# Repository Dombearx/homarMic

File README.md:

# homarMic: pilot głosowy

Mały bezprzewodowy mikrofon „naciśnij i mów" do asystenta działającego na
komputerze w sieci domowej. Przytrzymujesz przycisk, mówisz, puszczasz.
Nagranie trafia po Wi-Fi do serwera na komputerze, a dioda potwierdza odbiór.
Między poleceniami urządzenie śpi, więc bateria starcza na tygodnie.

| | Wersja bazowa | Wersja z głośnikiem |
|---|---|---|
| Wymiary | 37 × 69 × 21 mm | 37 × 103 × 21 mm |
| Potwierdzenie | dioda RGB | dioda RGB + odpowiedź głosowa |
| Koszt części (1 szt.) | ok. 60–90 zł | ok. 75–115 zł |
| Czas pracy (30 poleceń dziennie) | ok. 2 miesiące | ok. 3–4 tygodnie |

Skąd te liczby i jak wypada własne PCB na 10 sztuk:
[docs/wybor-czesci-i-koszty.md](docs/wybor-czesci-i-koszty.md).

> **Stan projektu.** Nic z tego nie zostało jeszcze fizycznie zbudowane.
> Płytki przechodzą kontrolę DRC w KiCadzie (0 błędów elektrycznych, 0
> niepołączonych padów), modele obudowy sprawdziłem na kolizje, serwer
> przetestowałem symulowanym pilotem. Firmware'u nie udało się skompilować w
> środowisku, w którym powstał (brak dostępu do narzędzi ESP32); przeszedł tylko
> kontrolę składni. Zbuduj najpierw jedną sztukę i dopiero potem zamawiaj części
> na kolejne. Lista rzeczy do sprawdzenia jest na końcu.

## Zawartość

| Katalog | Co tam jest |
|---|---|
| `pcb/` | płytki KiCad (`voice-mic`, `voice-mic-dock`), gotowe paczki Gerber w `pcb/gerber/`, skrypt generujący |
| `case/` | model OpenSCAD i gotowe pliki STL w `case/stl/` |
| `firmware/` | program dla XIAO ESP32-S3 (PlatformIO / Arduino) |
| `server/` | serwer odbiorczy w Pythonie i symulator pilota |
| `docs/` | wybór części, kosztorysy, czas pracy |

## Jak to działa

1. Naciśnięcie przycisku budzi układ. Nagrywanie rusza po ok. 0,3 s; dioda
   zapala się na **niebiesko** dopiero wtedy, gdy mikrofon naprawdę słucha.
2. Wi-Fi łączy się w tle (ok. 1–2 s), a dźwięk w tym czasie trafia do pamięci,
   więc początek polecenia nie przepada.
3. Po puszczeniu przycisku dioda świeci na **żółto**, aż serwer odpowie.
4. **Zielony** = serwer odebrał nagranie (kod HTTP 2xx). W wersji z głośnikiem
   pilot odtwarza wtedy odpowiedź, jeśli serwer ją odesłał.
5. Układ zasypia.

| Dioda | Znaczenie |
|---|---|
| niebieska | nagrywam, mów |
| żółta | wysyłam / czekam na odpowiedź |
| zielona | polecenie odebrane |
| 3 × czerwona | błąd: brak Wi-Fi, serwer nie odpowiada albo zwrócił błąd |
| 2 × długa czerwona po poleceniu | słaba bateria, odłóż do stacji |
| 2 × biała | po włączeniu zasilania: układ działa (czerwona = słaba bateria) |

Naciśnięcie krótsze niż 0,25 s jest ignorowane. Jedno polecenie może trwać do
30 s.

## Lista części

Ceny orientacyjne z listopada 2026. Niższa wartość to AliExpress, wyższa to
polskie sklepy.

### Pilot, wersja bazowa

| Oznaczenie | Część | Szt. | Cena |
|---|---|---|---|
| U1 | Seeed Studio XIAO ESP32-S3 (zwykły, nie Sense, nie Plus), z antenką | 1 | 30–45 zł |
| — | moduł mikrofonu I2S INMP441 (okrągły, 14 mm) | 1 | 7–15 zł |
| — | akumulator LiPo 3,7 V 500 mAh typu 502535 **z zabezpieczeniem** (PCM) | 1 | 12–20 zł |
| — | płytka `voice-mic` | 1 | 5–8 zł |
| SW1 | mikroprzycisk 6 × 6 mm, THT, wysokość 5 mm | 1 | 0,30 zł |
| D1 | dioda RGB 5 mm, wspólna katoda, matowa | 1 | 0,50 zł |
| D2 | dioda Schottky'ego SS14 (SMA) | 1 | 0,30 zł |
| R1 | 470 Ω, 1206 | 1 | grosze |
| R2, R3 | 220 Ω, 1206 | 2 | |
| R4 | 100 kΩ, 1206 | 1 | |
| R5, R6 | 470 kΩ, 1206 | 2 | |
| C1 | 100 nF, 1206 | 1 | |
| — | wkręty M2 × 12 (do plastiku lub zwykłe) | 4 | 1 zł |
| — | śruby M3 × 8 z łbem kulistym na imbus (ISO 7380) + nakrętki M3 | 2 + 2 | 1 zł |
| — | magnes neodymowy 8 × 3 mm | 1 | 1 zł |
| — | przewód cienki (np. kynar/silikon 28–30 AWG), ok. 40 cm | | |
| — | filament PETG lub PLA, ok. 25 g | | 2 zł |

### Dodatkowo w wersji z głośnikiem

| Oznaczenie | Część | Szt. | Cena |
|---|---|---|---|
| — | moduł wzmacniacza I2S MAX98357A (układ pinów jak Adafruit: LRC, BCLK, DIN, GAIN, SD, GND, VIN) | 1 | 8–15 zł |
| — | głośnik 28 mm, 8 Ω, 1–2 W | 1 | 5–8 zł |
| R7 | 10 kΩ, 1206 | 1 | grosze |
| C2 | 10 µF, 1206 | 1 | grosze |
| — | wkręty M2 × 12 | 2 | |

### Stacja dokująca

| Część | Szt. | Cena |
|---|---|---|
| płytka `voice-mic-dock` | 1 | 3 zł |
| pin sprężynowy (pogo) do lutowania THT, średnica korpusu 2 mm, wysokość ok. 7 mm, trzpień do 1,2 mm | 2 | 2–4 zł |
| magnes neodymowy 8 × 3 mm | 1 | 1 zł |
| przewód USB (stary kabel z wtykiem USB-A lub gniazdo USB-C „breakout" z rezystorami 5,1 kΩ) | 1 | 0–4 zł |
| wkręty M2 × 5 | 2 | |
| filament, ok. 35 g | | 3 zł |

Jedna stacja może obsługiwać kilka pilotów po kolei. Ładowanie do pełna trwa
ok. 10–11 h (XIAO ładuje prądem 50 mA), więc najwygodniej, żeby pilot po
prostu stał w stacji, gdy go nie używasz.

## Krok 1. Zamów płytki

Paczki `pcb/gerber/voice-mic-gerber.zip` i `pcb/gerber/voice-mic-dock-gerber.zip`
wgraj jako dwa osobne zamówienia (JLCPCB, PCBWay, Aisler). Parametry:
2 warstwy, FR-4, **1,6 mm**, miedź 1 oz, dowolny kolor, wykończenie HASL.
Minimalna ilość to zwykle 5 sztuk, czyli od razu masz płytki na 5 pilotów.

## Krok 2. Wydrukuj obudowę

Pliki z `case/stl/`. PETG lub PLA, warstwa 0,2 mm, 3 obrysy, wypełnienie 20%,
**bez podpór**. Części są już ułożone do druku.

| Plik | Ułożenie |
|---|---|
| `tub.stl` / `tub-speaker.stl` | przednią ścianką do stołu |
| `lid.stl` / `lid-speaker.stl` | zewnętrzną stroną do stołu |
| `button.stl` | klawiszem do stołu |
| `dock.stl` | tak jak stoi |

Wymiary zmienisz w `case/voice_mic.scad` (wszystko jest w parametrach na
górze pliku), a potem:

```bash
openscad -D 'part="tub"' -D speaker=false -o tub.stl voice_mic.scad
```

Najczęściej trzeba będzie dopasować `mic_shape` / `mic_d` (moduły INMP441
bywają okrągłe albo kwadratowe 14 × 14 mm) oraz `pogo_body` i `pogo_hole` do
kupionych pinów pogo.

## Krok 3. Zlutuj płytkę pilota

Wszystko da się zlutować zwykłą lutownicą z cienkim grotem. Kolejność ma
znaczenie.

1. **Elementy SMD** (przód płytki): R1–R6, C1, D2. Pasek na D2 (katoda) jest
   po stronie dolnej krawędzi płytki, czyli od strony USB. W wersji z
   głośnikiem także R7 i C2.
2. **Moduł XIAO.** Połóż go płasko na przedzie płytki, gniazdem USB w stronę
   dolnej krawędzi (gniazdo wystaje ok. 1,5 mm poza płytkę). Wyrównaj pady
   krawędziowe, przylutuj dwa po przekątnej, sprawdź ułożenie, potem pozostałe
   12.
3. **Pady baterii XIAO.** Odwróć płytkę. Pod modułem są dwa owalne otwory
   opisane na tylnej stronie. Przyłóż grot do otworu, podaj cynę i trzymaj
   2–3 s, aż wypełni otwór i złapie pad na spodzie modułu. Zrób to dla obu.
   Bez tego pilot działa tylko z USB.
4. **Przycisk SW1.**
5. **Mikrofon.** Przylutuj 6 przewodów długości ok. 25 mm do pól `MIC`
   (VDD, GND, SD, SCK, WS, L/R) i do tak samo opisanych pól modułu INMP441.
   Kolejność pól na module bywa różna, kieruj się opisami, nie położeniem.
6. **Dioda D1.** Włóż ją w płytkę, ale jeszcze nie lutuj. Najdłuższa nóżka
   (wspólna katoda) idzie do drugiego otworu od lewej. Włóż płytkę do
   wydrukowanej wanny, dosuń diodę tak, żeby czubek był równo z powierzchnią
   obudowy, i dopiero wtedy przylutuj nóżki od tyłu.
7. **Antena.** Wepnij dołączoną antenkę w złącze na module XIAO.
8. **Wersja z głośnikiem:** moduł MAX98357A lutujesz od **tylnej** strony
   płytki do pól `AMP`, elementami do tyłu, tak żeby wystawał ponad górną
   krawędź płytki. Opisy pól na płytce (VIN, GND, SD, GAIN, DIN, BCLK, LRC)
   muszą się pokryć z opisami na module. Głośnik przylutuj dwoma przewodami do
   wyjścia modułu.

Baterii jeszcze nie podłączaj.

## Krok 4. Wgraj program i przetestuj na kablu

```bash
cd firmware
cp include/config.example.h include/config.h
```

W `include/config.h` wpisz nazwę i hasło Wi-Fi, adres komputera z asystentem
i ewentualnie `HAS_SPEAKER 1`. Potem podłącz pilota kablem USB-C:

```bash
pio run -t upload
```

```bash
pio device monitor
```

Jeśli komputer nie widzi portu, przytrzymaj malutki przycisk `B` (BOOT) na
module XIAO i dopiero wtedy wepnij kabel. To samo zrób przy każdym kolejnym
wgrywaniu, bo śpiący układ odłącza się od USB.

W Arduino IDE: płytka „XIAO_ESP32S3", **PSRAM: OPI PSRAM**, USB CDC On Boot:
Enabled; pliki `src/main.cpp` i `include/config.h` wrzuć do jednego szkicu.

Uruchom serwer (krok 6), przytrzymaj przycisk, powiedz coś, puść. Powinieneś
zobaczyć niebieski, żółty i zielony, a w katalogu `server/recordings/` plik
WAV. Odsłuchaj go. Jeśli jest za cicho lub przesterowane, zmień
`MIC_GAIN_SHIFT` w `config.h`. Jeśli kolory diody są zamienione (diody RGB
mają różne układy nóżek), zamień numery `PIN_LED_R/G/B` w `main.cpp`.

## Krok 5. Bateria, styki i składanie

1. **Bateria.** Sprawdź miernikiem biegunowość przewodów. Czerwony do `BAT+`,
   czarny do `BAT-`. Lutuj po jednym przewodzie i nie zwieraj ich ze sobą.
   Po podłączeniu dioda mignie dwa razy na biało.
2. **Styki ładowania.** W dolną ściankę wanny wkręć od zewnątrz dwie śruby
   M3 × 8. Od środka załóż na każdą oczko z odizolowanego przewodu i dokręć
   nakrętką. Patrząc od przodu (przycisk do ciebie, USB na dole): lewa śruba
   to `DOCK+`, prawa `DOCK-`. Przylutuj przewody do tak opisanych pól płytki.
   Na stykach nie ma napięcia, gdy pilot nie stoi w stacji.
3. **Magnes.** Wklej magnes w okrągłe gniazdo w dolnej ściance (od środka,
   między śrubami). Zrób to przed włożeniem płytki.
4. Włóż klawisz w otwór wanny (kołnierzem do środka).
5. Wsuń moduł mikrofonu w okrągłe gniazdo na przedniej ściance, **stroną z
   otworkiem do ścianki**, puszką mikrofonu do środka. Przyklej kroplą kleju
   przy krawędzi, nie zalewając otworka.
6. Wersja z głośnikiem: wklej głośnik membraną do kratki.
7. Połóż płytkę na słupkach, gniazdem USB w otwór dolnej ścianki.
8. Baterię przyklej taśmą piankową do tyłu płytki, między tulejami pokrywy.
   Antenę przyklej do bocznej ścianki, z dala od baterii.
9. Załóż pokrywę i skręć czterema wkrętami M2 × 12 (sześcioma w wersji z
   głośnikiem). Wkręty przechodzą przez płytkę i trzymają wszystko razem.

## Krok 6. Stacja dokująca

1. Wklej magnes w gniazdo od spodu podłogi stacji. **Sprawdź biegun:** musi
   przyciągać magnes w pilocie, nie odpychać.
2. Przylutuj dwa piny pogo do płytki stacji, a do pól `+` i `-` przewód 5 V
   z kabla USB (czerwony = +5 V, czarny = masa).
3. Wsuń płytkę pinami do góry w komorę od spodu i przykręć dwoma wkrętami
   M2 × 5. Piny powinny wystawać ok. 1,3 mm ponad podłogę. Pin `+5V` musi
   wypaść pod lewą śrubą pilota (patrząc od strony wycięcia w stacji).
4. Przewód wyprowadź kanałem do tyłu i unieruchom kroplą kleju.
5. Zmierz miernikiem: między pinami ma być 5 V, plus po właściwej stronie.

Pilot wstawiasz przyciskiem w stronę wycięcia. Włożony odwrotnie po prostu
się nie ładuje (dioda D2 chroni przed odwrotną biegunowością). Ładowanie
sygnalizuje czerwona dioda na module XIAO, widoczna przez szczelinę przy
gnieździe USB.

## Krok 7. Serwer na komputerze

Serwer wzorcowy nie ma żadnych zależności poza Pythonem 3.8+:

```bash
python3 server/voice_server.py --port 8765
```

Zapisuje każde polecenie jako WAV (16 kHz, 16 bit, mono) w `recordings/`.
Żeby od razu przekazywać nagrania do agenta:

```bash
python3 server/voice_server.py --exec "python3 moj_agent.py"
```

Po każdym nagraniu uruchomi się `moj_agent.py <ścieżka.wav>`. Jeśli program
wypisze na standardowe wyjście ścieżkę do pliku `.wav`, a pilot ma głośnik,
ten plik wróci do pilota jako odpowiedź głosowa (WAV, PCM 16 bit, mono,
najlepiej 16–24 kHz).

Możesz też wbudować odbiór we własnego agenta:

```python
from voice_server import serve

def handle(wav_path, meta):   # meta: device, battery_mv, speaker, seconds
    tekst = transkrybuj(wav_path)      # np. faster-whisper
    odpowiedz = agent(tekst, zrodlo=meta["device"])
    return None                        # albo ścieżka / bajty WAV z odpowiedzią

serve(handle, port=8765)
```

Zielona dioda zapala się dopiero, gdy `handle` się zakończy, więc jeśli agent
myśli długo, uruchom go w tle i wróć od razu. Wyjątek w `handle` daje kod 500
i czerwoną diodę.

Bez pilota przetestujesz serwer tak:

```bash
python3 server/fake_mic.py --host 127.0.0.1
```

Zapora systemowa musi przepuszczać port 8765 z sieci lokalnej. Komputerowi
warto nadać stały adres IP w routerze.

### Protokół (gdybyś pisał własny odbiornik)

```
POST /api/voice HTTP/1.1
Transfer-Encoding: chunked
Content-Type: application/octet-stream
X-Audio-Format: pcm_s16le
X-Sample-Rate: 16000
X-Channels: 1
X-Device-Id: mic-a1b2c3        nazwa pilota (z config.h albo z adresu MAC)
X-Battery-Mv: 3912
X-Speaker: 0                   1 = pilot potrafi odtworzyć odpowiedź
X-Auth-Token: ...              tylko gdy ustawiony w config.h

<surowe próbki PCM, little-endian>
```

Odpowiedź: dowolny kod 2xx oznacza „odebrane". Jeśli `Content-Type` to
`audio/wav` i podany jest `Content-Length`, wersja z głośnikiem odtworzy
treść. Odpowiedź musi mieć `Content-Length` (bez `chunked`). Na odpowiedź
pilot czeka do 30 s.

## Wiele pilotów

Każdy pilot ma ten sam program. Rozróżnia je nagłówek `X-Device-Id`; domyślnie
to `mic-` plus końcówka adresu MAC, a w `config.h` możesz wpisać własną nazwę
(np. `kuchnia`) przed wgraniem. Serwer obsługuje wiele pilotów jednocześnie.

## Problemy

| Objaw | Co sprawdzić |
|---|---|
| Działa na USB, nie działa na baterii | otwory `BAT+`/`BAT-` pod XIAO nie złapały padów modułu; dolutuj od tyłu |
| 3 × czerwona zaraz po puszczeniu | serwer nie działa, zły adres w `config.h` albo zapora |
| 3 × czerwona po ok. 10 s | brak połączenia z Wi-Fi (hasło, zasięg, sieć tylko 5 GHz; ESP32 potrzebuje 2,4 GHz) |
| Nagranie to cisza | zamienione przewody SD/SCK/WS albo `L/R` nie jest na masie |
| Ucięty początek polecenia | zacznij mówić, gdy zapali się niebieska dioda |
| Klawisz nie klika albo jest stale wciśnięty | inna wysokość mikroprzycisku; zmień `sw_h` w pliku SCAD |
| Nie ładuje w stacji | odwrócona biegunowość pinów, za krótkie piny, magnes odpycha |
| Bateria pada po kilku dniach | zmierz prąd uśpienia (powinno być ok. 20 µA); patrz niżej |

## Do sprawdzenia przy pierwszej sztuce

- Kompilacja firmware'u prawdziwym narzędziem (PlatformIO). Program używa
  starszego sterownika I2S (`driver/i2s.h`), który działa z rdzeniem Arduino
  ESP32 2.x i 3.x.
- Prąd uśpienia. Seeed podaje 14 µA dla XIAO ESP32-S3, dzielnik baterii
  dokłada ok. 4,5 µA. Niektóre niezależne pomiary pokazują wyraźnie więcej,
  więc zmierz to miernikiem włączonym szeregowo z baterią.
- Dopasowanie modułu INMP441 do gniazda i pinów pogo do stacji (części z
  AliExpress różnią się wymiarami między sprzedawcami).
- Siła magnesu względem nacisku pinów pogo: pilot ma sam dosiadać w stacji.
  Jeśli „pływa" na pinach, weź piny o mniejszym nacisku albo mocniejszy
  magnes (parametry `magnet_d`, `magnet_h`).
- Luz klawisza i głębokość gniazda USB-C z twoim kablem.

## Zmiany w płytce

Płytki powstają ze skryptu `pcb/gen_pcb.py` (wymaga KiCada 7 lub nowszego z
modułem `pcbnew`); rozmieszczenie, sieci i opisy są w nim zapisane wprost,
a ścieżki prowadzi `pcb/router.py`. Pliki `.kicad_pcb` można też po prostu
otworzyć i poprawić ręcznie w KiCadzie. Schemat połączeń jest w
[docs/wybor-czesci-i-koszty.md](docs/wybor-czesci-i-koszty.md#schemat-połączeń).
Wymiary padów modułu XIAO pochodzą z biblioteki Seeed Studio OPL (CC BY-SA 4.0).

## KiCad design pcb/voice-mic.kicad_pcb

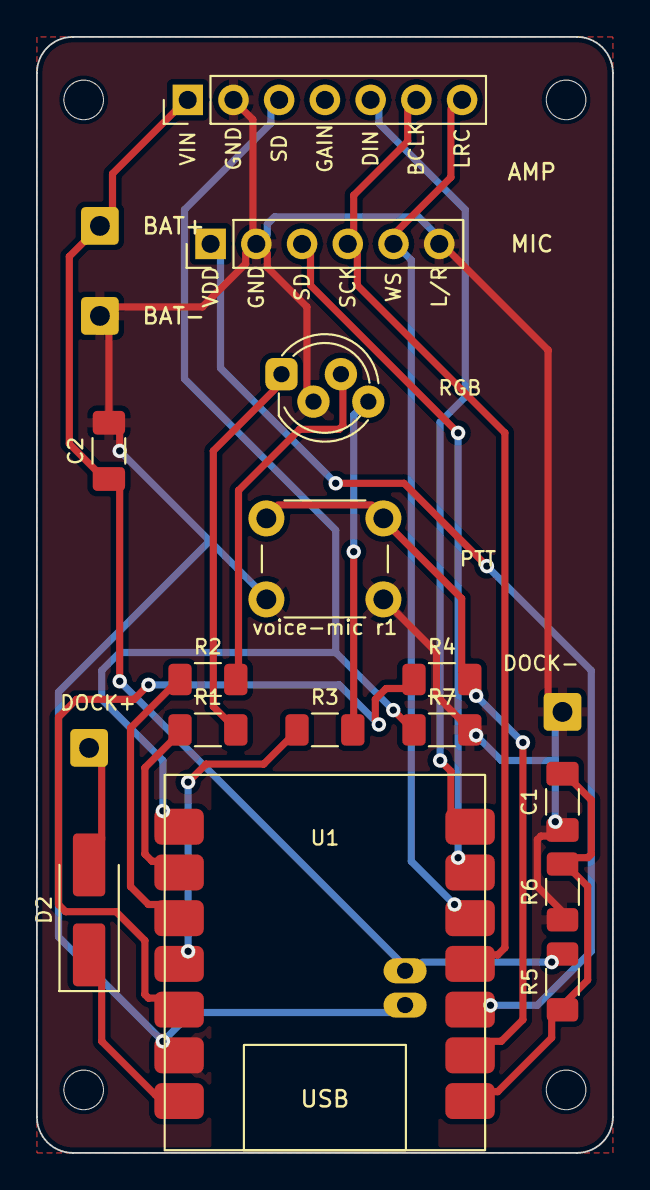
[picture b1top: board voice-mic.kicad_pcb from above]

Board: 2 copper layers, 32.0 x 62.0 mm, 23 parts (0 on the bottom side), 19 nets.

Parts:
C1: 100n; C_1206_3216Metric_Pad1.33x1.80mm_HandSolder
C2: 10u; C_1206_3216Metric_Pad1.33x1.80mm_HandSolder
D1: RGB 5mm wsp. katoda; LED_D5.0mm-4_RGB_Staggered_Pins
D2: SS14; D_SMA_Handsoldering
H1, H2, H3, H4: M2; MountingHole_2.2mm_M2
J1: INMP441; PinHeader_1x06_P2.54mm_Vertical
J2: MAX98357A; PinHeader_1x07_P2.54mm_Vertical
J3: BAT+; SolderWire-0.5sqmm_1x01_D0.9mm_OD2.1mm
J4: DOCK+; SolderWire-0.5sqmm_1x01_D0.9mm_OD2.1mm
J5: DOCK-; SolderWire-0.5sqmm_1x01_D0.9mm_OD2.1mm
J6: BAT-; SolderWire-0.5sqmm_1x01_D0.9mm_OD2.1mm
R1: 470R; R_1206_3216Metric_Pad1.30x1.75mm_HandSolder
R2, R3: 220R; R_1206_3216Metric_Pad1.30x1.75mm_HandSolder
R4: 100k; R_1206_3216Metric_Pad1.30x1.75mm_HandSolder
R5, R6: 470k; R_1206_3216Metric_Pad1.30x1.75mm_HandSolder
R7: 10k; R_1206_3216Metric_Pad1.30x1.75mm_HandSolder
SW1: 6x6x5; SW_PUSH_6mm_H5mm
U1: XIAO ESP32-S3

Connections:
+3V3: R4.1, U1.12
AMP_DIN: J2.5, U1.7
AMP_SD: J2.3, R7.1, U1.8
BAT_SENSE: C1.2, R5.1, R6.2, U1.1
BTN: R4.2, SW1.1, U1.2
DOCK_P: D2.2, J4.1
GND: C1.1, C2.2, D1.2, J1.2, J1.6, J2.2, J5.1, J6.1, R6.1, R7.2, SW1.2, U1.13, U1.24
I2S_BCLK: J1.4, J2.6, U1.4
I2S_WS: J1.5, J2.7, U1.5
LED_B: R3.1, U1.11
LED_BA: D1.4, R3.2
LED_G: R2.1, U1.10
LED_GA: D1.3, R2.2
LED_R: R1.1, U1.9
LED_RA: D1.1, R1.2
MIC_PWR: J1.1, U1.3
MIC_SD: J1.3, U1.6
VBAT: C2.1, J2.1, J3.1, R5.2, U1.23
VBUS: D2.1, U1.14

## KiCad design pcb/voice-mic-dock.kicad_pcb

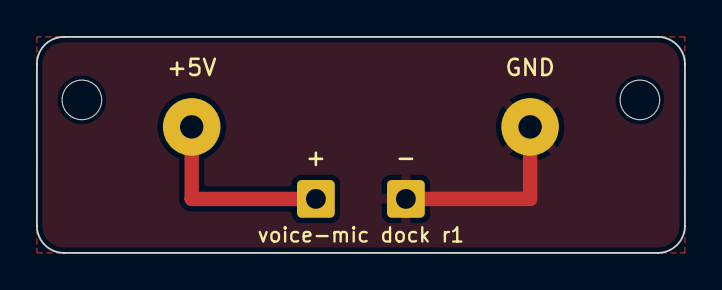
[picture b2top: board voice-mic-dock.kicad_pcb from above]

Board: 2 copper layers, 36.0 x 12.0 mm, 5 parts (0 on the bottom side), 2 nets.

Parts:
H1, H2: M2; MountingHole_2.2mm_M2
J1: +5V; SolderWire-0.5sqmm_1x01_D0.9mm_OD2.1mm
J2: GND; SolderWire-0.5sqmm_1x01_D0.9mm_OD2.1mm
P1: pogo x2

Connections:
+5V: J1.1, P1.1
GND: J2.1, P1.2

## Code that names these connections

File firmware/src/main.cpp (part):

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
// --- wyprowadzenia (XIAO ESP32-S3) ---
static const int PIN_BAT      = 1;   // D0  dzielnik 1:2 napiecia baterii
static const int PIN_BTN      = 2;   // D1  przycisk do masy, wybudzanie
static const int PIN_MIC_PWR  = 3;   // D2  zasilanie mikrofonu
static const int PIN_I2S_BCLK = 4;   // D3
static const int PIN_I2S_WS   = 5;   // D4
static const int PIN_MIC_SD   = 6;   // D5
static const int PIN_AMP_DIN  = 43;  // D6
static const int PIN_AMP_SD   = 44;  // D7  wlaczenie wzmacniacza
static const int PIN_LED_R    = 7;   // D8
static const int PIN_LED_G    = 8;   // D9
static const int PIN_LED_B    = 9;   // D10

static const int SAMPLE_RATE = 16000;
static const uint32_t MIN_PRESS_MS  = 250;    // krotsze nacisniecie = pomylka
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
static void led(Color c) {
  const bool on = LED_COMMON_CATHODE ? HIGH : LOW;
  digitalWrite(PIN_LED_R, (c & 1) ? on : !on);
  digitalWrite(PIN_LED_G, (c & 2) ? on : !on);
  digitalWrite(PIN_LED_B, (c & 4) ? on : !on);
}

static void blink(Color c, int times, int onMs = 120, int offMs = 120) {
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    while (!recDone) delay(5);
    i2s_driver_uninstall(I2S_NUM_0);
  }
  digitalWrite(PIN_AMP_SD, LOW);
  digitalWrite(PIN_MIC_PWR, LOW);
  WiFi.disconnect(true);
  WiFi.mode(WIFI_OFF);
  // nie zasypiaj z wcisnietym przyciskiem - uklad obudzilby sie od razu
  uint32_t t0 = millis();
  while (digitalRead(PIN_BTN) == LOW && millis() - t0 < 10000) delay(10);
  delay(30);
  esp_sleep_enable_ext0_wakeup((gpio_num_t)PIN_BTN, 0);
  Serial.println("sleep");
  esp_deep_sleep_start();
}
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  cfg.dma_buf_len = 256;
  i2s_pin_config_t pins = {};
  pins.mck_io_num = I2S_PIN_NO_CHANGE;
  pins.bck_io_num = PIN_I2S_BCLK;
  pins.ws_io_num = PIN_I2S_WS;
  pins.data_out_num = I2S_PIN_NO_CHANGE;
  pins.data_in_num = PIN_MIC_SD;
  i2s_driver_install(I2S_NUM_0, &cfg, 0, nullptr);
  i2s_set_pin(I2S_NUM_0, &pins);
}
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  cfg.tx_desc_auto_clear = true;
  i2s_pin_config_t pins = {};
  pins.mck_io_num = I2S_PIN_NO_CHANGE;
  pins.bck_io_num = PIN_I2S_BCLK;
  pins.ws_io_num = PIN_I2S_WS;
  pins.data_out_num = PIN_AMP_DIN;
  pins.data_in_num = I2S_PIN_NO_CHANGE;
  i2s_driver_install(I2S_NUM_0, &cfg, 0, nullptr);
  i2s_set_pin(I2S_NUM_0, &pins);
  digitalWrite(PIN_AMP_SD, HIGH);

  static uint8_t in[1024];
  static int16_t out[1024];
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  size_t written;
  for (int i = 0; i < 3; i++) i2s_write(I2S_NUM_0, out, sizeof(out), &written, portMAX_DELAY);
  delay(60);
  digitalWrite(PIN_AMP_SD, LOW);
}
#endif

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}

void setup() {
  rtc_gpio_deinit((gpio_num_t)PIN_BTN);            // po wybudzeniu pin nalezy jeszcze do domeny RTC
  pinMode(PIN_BTN, INPUT_PULLUP);
  pinMode(PIN_LED_R, OUTPUT); pinMode(PIN_LED_G, OUTPUT); pinMode(PIN_LED_B, OUTPUT);
  led(OFF);
  pinMode(PIN_AMP_SD, OUTPUT); digitalWrite(PIN_AMP_SD, LOW);
  pinMode(PIN_MIC_PWR, OUTPUT); digitalWrite(PIN_MIC_PWR, HIGH);
  Serial.begin(115200);
#if ARDUINO_USB_CDC_ON_BOOT
  Serial.setTxTimeoutMs(0);                        // bez komputera na USB logi nie moga blokowac
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
  const bool byButton = esp_sleep_get_wakeup_cause() == ESP_SLEEP_WAKEUP_EXT0;
  const int mv = batteryMv();
  if (!byButton && digitalRead(PIN_BTN) == HIGH) {
    // wlaczenie zasilania lub reset: pokaz stan baterii i idz spac
    delay(300);
    Serial.printf("voice-mic %s, bateria %d mV\n", FW_VERSION, mv);
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  // 2. dopoki przycisk jest wcisniety (plus krotka dogrywka) - nagrywaj i wysylaj na biezaco
  while (true) {
    const uint32_t now = millis();
    if (!tRelease && (digitalRead(PIN_BTN) == HIGH || recLen >= recCap)) {
      tRelease = now;
      if (now - tStart < MIN_PRESS_MS) goToSleep();
    }
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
